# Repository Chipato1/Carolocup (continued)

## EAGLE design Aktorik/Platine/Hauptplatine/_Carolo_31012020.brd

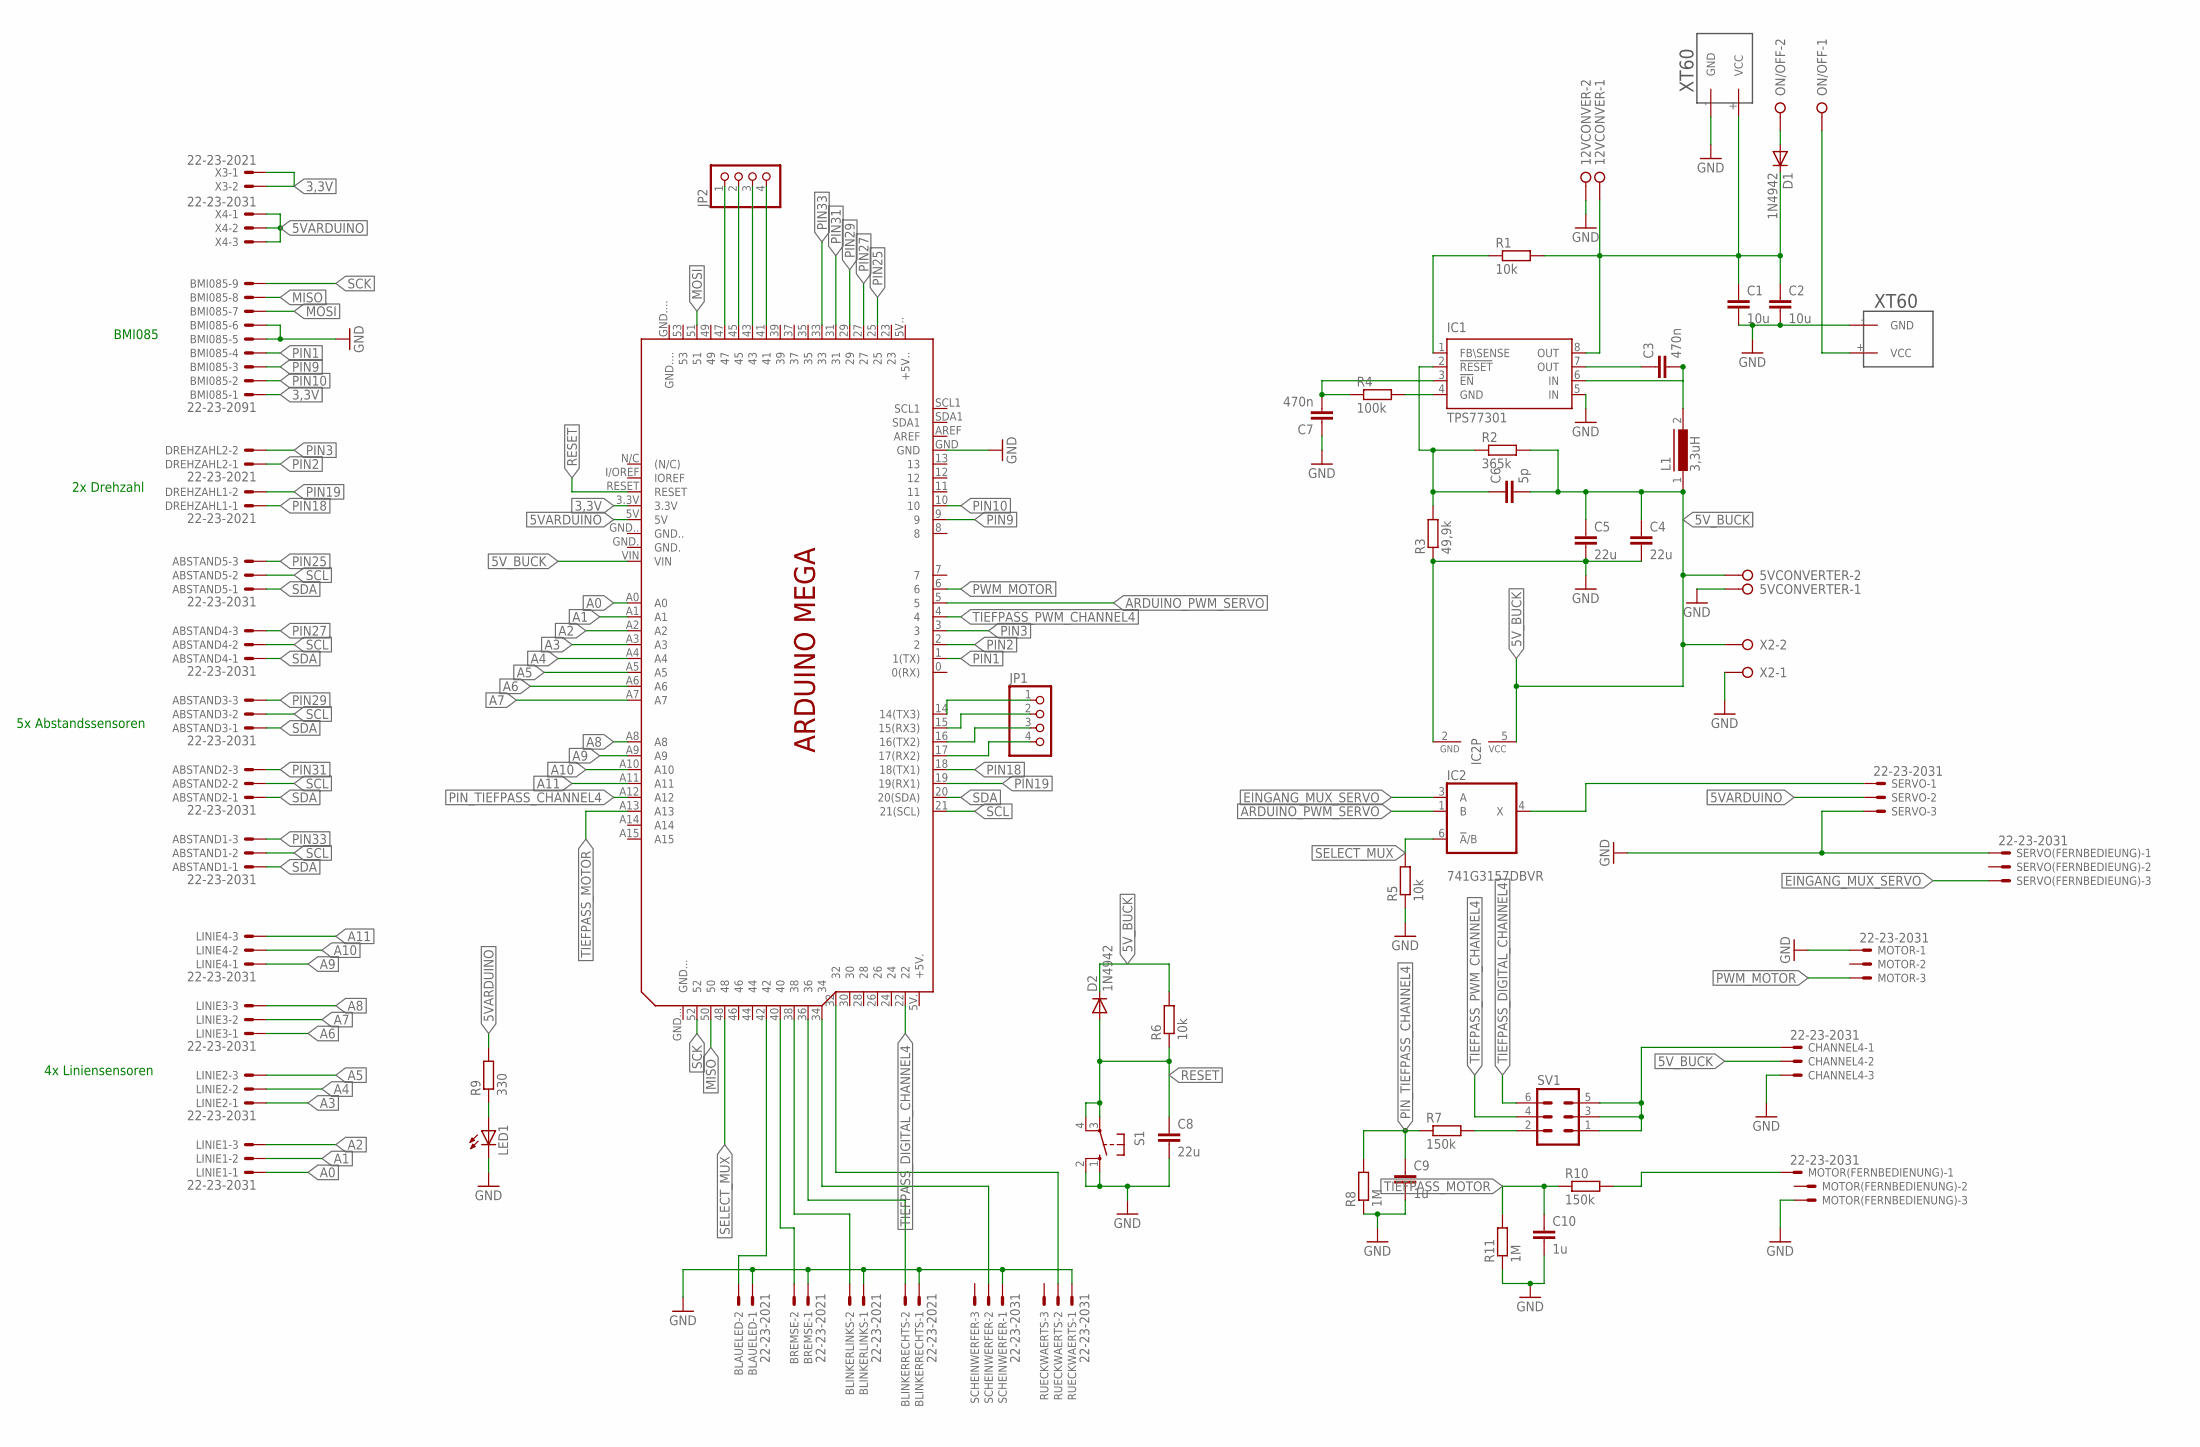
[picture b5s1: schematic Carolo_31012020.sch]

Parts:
5VCONVERTER, 12VCONVER: W237-02P; W237-132
ABSTAND1, ABSTAND2, ABSTAND3, ABSTAND4, ABSTAND5: 22-23-2031
BLAUELED: 22-23-2021
BLINKERLINKS: 22-23-2021
BLINKERRECHTS: 22-23-2021
BMI085: 22-23-2091
BREMSE: 22-23-2021
C1, C2: 10u; C2.5-3
C3, C7: 470n; C2.5-3
C4, C5, C8: 22u; C2.5-3
C6: 5p; C2.5-3
C9, C10: 1u; C2.5-3
CHANNEL4: 22-23-2031
D1, D2: 1N4942; DO41-10
DREHZAHL1, DREHZAHL2: 22-23-2021
IC1: TPS77301; SOP-08
IC2: 741G3157DBVR; DBV_R-PDSO-G6
JP1, JP2: PINHD-1X4; 1X04
L1: 3,3uH; 82114R
LED1: LED5MM
LINIE1, LINIE2, LINIE3, LINIE4: 22-23-2031
MOTOR: 22-23-2031
MOTOR(FERNBEDIENUNG): 22-23-2031
ON/OFF: W237-02P; W237-132
PCB1: ARDUINO_MEGA
R1, R5, R6: 10k; 0411/15
R2: 365k; 0411/15
R3: 49,9k; 0411/15
R4: 100k; 0411/15
R7, R10: 150k; 0411/15
R8, R11: 1M; 0411/15
R9: 330; 0411/15
RUECKWAERTS: 22-23-2031
S1: 10-XX; B3F-10XX
SCHEINWERFER: 22-23-2031
SERVO: 22-23-2031
SERVO(FERNBEDIEUNG): 22-23-2031
SV1: ML6
U$1, U$2: XT60
X2: W237-02P; W237-132
X3: 22-23-2021
X4: 22-23-2031

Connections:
3,3V: BMI085.1, PCB1.3.3V, X3.1, X3.2
5VARDUINO: PCB1.5V, R9.2, SERVO.2, X4.1, X4.2, X4.3
5V_BUCK: 5VCONVERTER.2, C4.1, C5.1, C6.2, CHANNEL4.2, D2.C, IC2.5 (VCC), L1.1, PCB1.VIN, R2.2, R6.2, X2.2
A0: LINIE1.1, PCB1.A0
A1: LINIE1.2, PCB1.A1
A2: LINIE1.3, PCB1.A2
A3: LINIE2.1, PCB1.A3
A4: LINIE2.2, PCB1.A4
A5: LINIE2.3, PCB1.A5
A6: LINIE3.1, PCB1.A6
A7: LINIE3.2, PCB1.A7
A8: LINIE3.3, PCB1.A8
A9: LINIE4.1, PCB1.A9
A10: LINIE4.2, PCB1.A10
A11: LINIE4.3, PCB1.A11
ARDUINO_PWM_SERVO: IC2.1 (B), PCB1.5
EINGANG_MUX_SERVO: IC2.3 (A), SERVO(FERNBEDIEUNG).3
GND: 5VCONVERTER.1, 12VCONVER.2, BLAUELED.1, BLINKERLINKS.1, BLINKERRECHTS.1, BMI085.5, BMI085.6, BREMSE.1, C1.2, C2.2, C4.2, C5.2, C7.1, C8.2, C9.2, C10.2, CHANNEL4.3, IC1.5 (IN), IC2.2 (GND), LED1.K (C), MOTOR.1, MOTOR(FERNBEDIENUNG).3, PCB1.GND, R3.1, R5.1, R8.1, R11.1, RUECKWAERTS.1, S1.1 (S), S1.2 (S1), SCHEINWERFER.1, SERVO.3, SERVO(FERNBEDIEUNG).1, U$1.- (GND), U$2.- (GND), X2.1
MISO: BMI085.8, PCB1.50; also elsewhere on the board
MOSI: BMI085.7, PCB1.51
unnamed: ON/OFF.1, U$1.+ (VCC)
unnamed: IC2.4 (X), SERVO.1
unnamed: R7.2, SV1.2
unnamed: C6.1, IC1.2 (!RESET), R2.1, R3.2
unnamed: C3.1, IC1.7 (OUT)
unnamed: CHANNEL4.1, SV1.1, SV1.3, SV1.5
unnamed: PCB1.32, RUECKWAERTS.2
unnamed: C3.2, IC1.6 (IN), L1.2
unnamed: C7.2, IC1.3 (!EN), R4.1
unnamed: PCB1.34, SCHEINWERFER.2
unnamed: BLINKERRECHTS.2, PCB1.36
unnamed: BLINKERLINKS.2, PCB1.38
unnamed: LED1.A, R9.1
unnamed: BLAUELED.2, PCB1.42
unnamed: BREMSE.2, PCB1.40
unnamed: JP2.4, PCB1.41
unnamed: IC1.4 (GND), R4.2
unnamed: D1.A, ON/OFF.2
unnamed: JP2.3, PCB1.43
unnamed: 12VCONVER.1, C1.1, C2.1, D1.C, IC1.8 (OUT), R1.2, U$2.+ (VCC)
unnamed: MOTOR(FERNBEDIENUNG).1, R10.2
unnamed 48: JP2.2, PCB1.45; also elsewhere on the board
unnamed 49: JP2.1, PCB1.47; also elsewhere on the board
unnamed: IC1.1 (FB\SENSE), R1.1
unnamed: JP1.1, PCB1.14 (14(TX3))
unnamed: JP1.2, PCB1.15 (15(RX3))
unnamed: JP1.3, PCB1.16 (16(TX2))
unnamed: JP1.4, PCB1.17 (17(RX2))
PIN1: BMI085.4, PCB1.1 (1(TX))
PIN2: DREHZAHL2.1, PCB1.2
PIN3: DREHZAHL2.2, PCB1.3
PIN9: BMI085.3, PCB1.9
PIN10: BMI085.2, PCB1.10
PIN18: DREHZAHL1.1, PCB1.18 (18(TX1)); also elsewhere on the board
PIN19: DREHZAHL1.2, PCB1.19 (19(RX1)); also elsewhere on the board
PIN25: ABSTAND5.3, PCB1.25
PIN27: ABSTAND4.3, PCB1.27
PIN29: ABSTAND3.3, PCB1.29
PIN31: ABSTAND2.3, PCB1.31
PIN33: ABSTAND1.3, PCB1.33
PIN_TIEFPASS_CHANNEL4: C9.1, PCB1.A12, R7.1, R8.2
PWM_MOTOR: MOTOR.3, PCB1.6
RESET: C8.1, D2.A, PCB1.RESET, R6.1, S1.3, S1.4 (P1)
SCK: BMI085.9, PCB1.52
SCL: ABSTAND1.2, ABSTAND2.2, ABSTAND3.2, ABSTAND4.2, ABSTAND5.2, PCB1.21 (21(SCL))
SDA: ABSTAND1.1, ABSTAND2.1, ABSTAND3.1, ABSTAND4.1, ABSTAND5.1, PCB1.20 (20(SDA))
SELECT_MUX: IC2.6 (!A!/B), PCB1.48, R5.2
TIEFPASS_DIGITAL_CHANNEL4: PCB1.22, SV1.6
TIEFPASS_MOTOR: C10.1, PCB1.A13, R10.1, R11.2
TIEFPASS_PWM_CHANNEL4: PCB1.4, SV1.4

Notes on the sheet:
BMI085
2x Drehzahl
5x Abstandssensoren
4x Liniensensoren

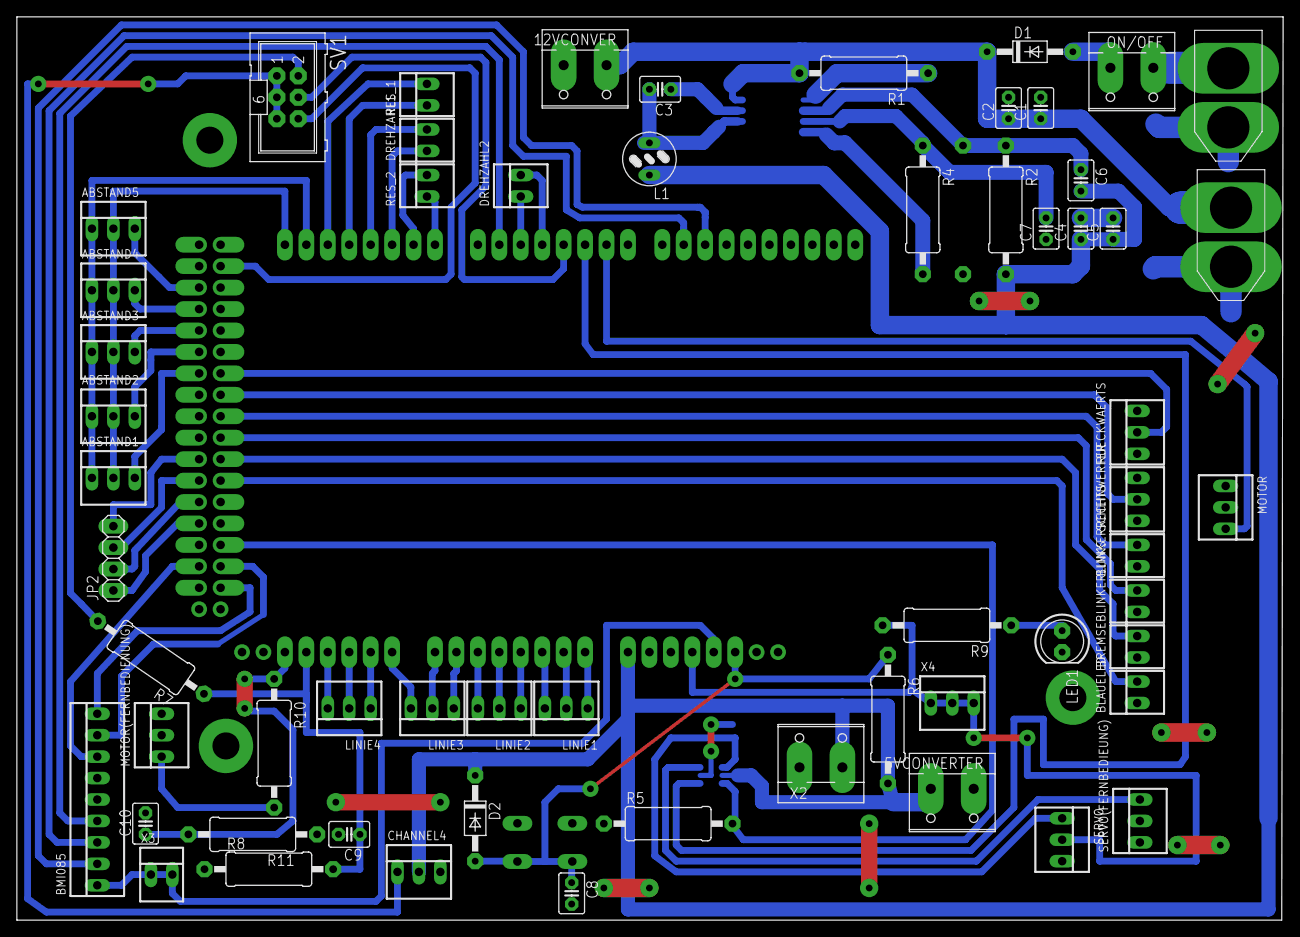
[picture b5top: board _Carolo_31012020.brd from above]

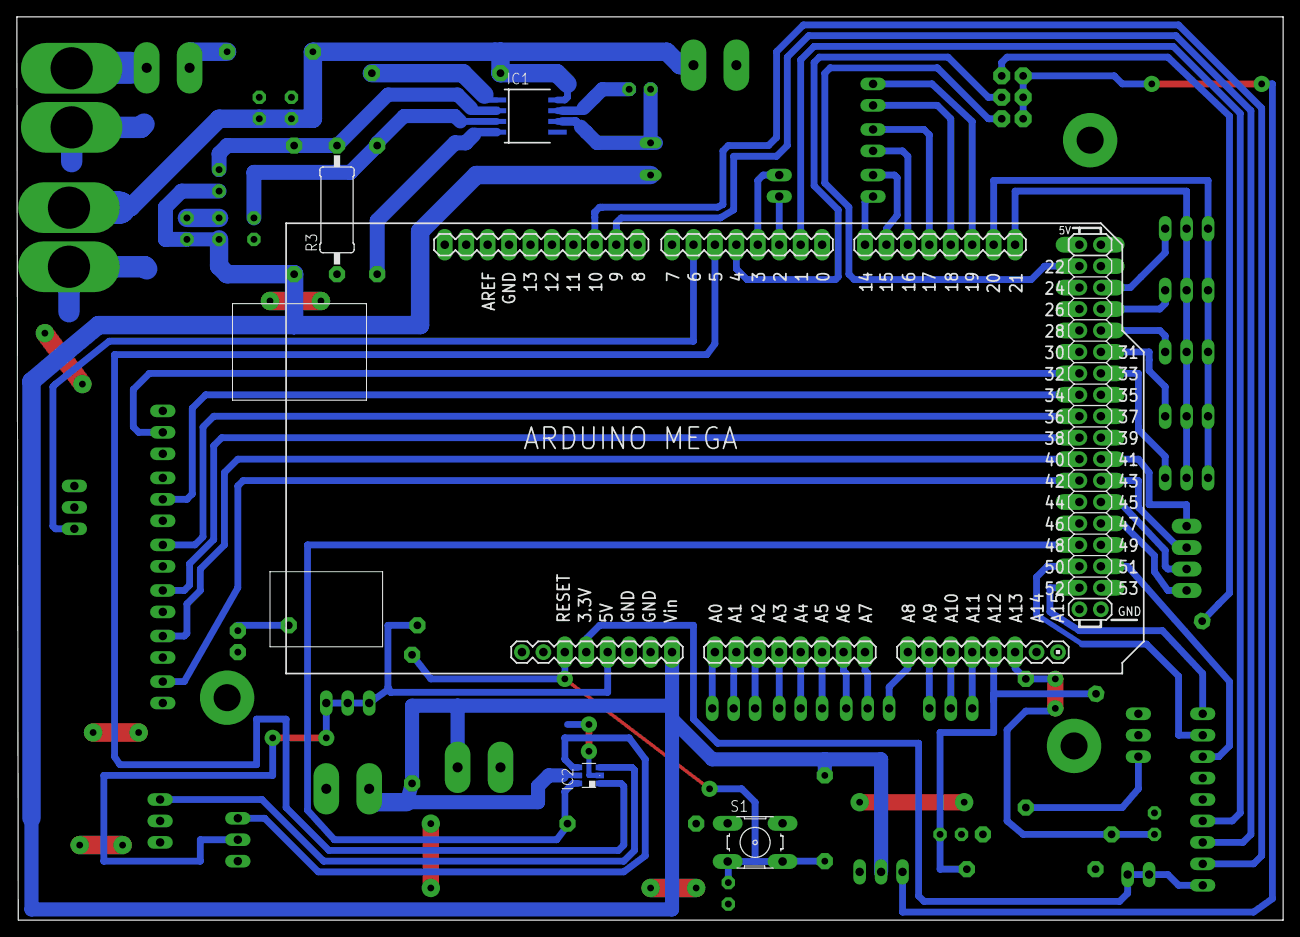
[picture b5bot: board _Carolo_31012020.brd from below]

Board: 2 copper layers, 150.0 x 107.0 mm, 64 parts (5 on the bottom side), 34 nets.

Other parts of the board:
E$1: ARDUINO_MEGA
RES_1, RES_2: 22-23-2021

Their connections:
MISO: E$1.50; also elsewhere on the board
unnamed 48: E$1.45; also elsewhere on the board
unnamed 49: E$1.47; also elsewhere on the board
PIN18: E$1.16; also elsewhere on the board
PIN19: E$1.17; also elsewhere on the board
S$1: E$1.19, RES_1.2
S$2: E$1.18, RES_1.1
S$3: E$1.15, RES_2.2
S$4: E$1.14, RES_2.1

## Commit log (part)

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2020-01-18 Added Start box detection
2020-01-18 Added new nodes
2020-01-18 Update CMakeLists
2020-01-18 Rename
2020-01-18 Name fix
2020-01-18 Name
2020-01-18 Typo
2020-01-18 Aktuell benötigte Nodes für die Kameraerkennung
2020-01-18 Create test
2020-01-18 new Upload
2020-01-18 Zweite Platine fertig
2020-01-20 ros erstellt
2020-01-20 Updated lane detection
2020-01-20 Added image proc
2020-01-20 Added launch script
2020-01-20 Kamera eingestellt und config hinzugefügt
2020-01-20 Config fix
2020-01-20 Fix for new clothoid model
2020-01-20 Added image view
2020-01-20 Added calibrate script
2020-01-20 Mem opti
2020-01-20 GPU Optimierungen
2020-01-20 Bug fix
2020-01-20 files
2020-01-20 RC motor hinzugefügt
2020-01-20 lichter knoten verschoben
2020-01-20 Revert "files"
    This reverts commit 8bc4316fc82aa183934083b4fa9890b025077f60.
2020-01-20 Revert "Merge pull request #60 from Chipato1/spurerkennung"
    This reverts commit 08e747200bb99e5533f0eb1627566205d3175c71, reversing
    changes made to ee4637fffe4195ab343a74071d12329f193db9f8.
2020-01-20 patch
2020-01-20 Gitignore CMakeLists.txt
2020-01-20 Added the stuff Alex deleted
2020-01-20 Commit für Branch
2020-01-20 test version
2020-01-20 Revert "patch"
    This reverts commit a01900fcba367d84bb3aac4d98ac42adad781406.
2020-01-20 Push it!
2020-01-20 alles murks
2020-01-21 Kamera neu eingestellt
2020-01-21 Fail
2020-01-21 rosserial als Paket abgelegt
2020-01-21 rosserial als Paket abgelegt und jetzt auch geaddet
2020-01-21 added behavior tree to master
2020-01-22 patch2.0
2020-01-22 revision abgeschlossen, erfolgreiches überprüfen
2020-01-22 Versuch
2020-01-22 Patch für Arduino und Tester Node
2020-01-22 ros anpassungen
2020-01-22 Created trajectory node; removed empty Behavior-Tree node
2020-01-23 kommentare hinzugefügt+RC mode fix
2020-01-23 Update algorithm & added ros package
2020-01-23 Updated launch script
2020-01-23 Added compiler flags
2020-01-23 Add files via upload
    arduino code sensorik
2020-01-23 Add files via upload
    Code for whole arduino (sensorik and aktorik)
2020-01-23 names changed
2020-01-23 name changed
2020-01-23 imu and tof fixed
2020-01-23 Updated ROS node
2020-01-23 Updated package
2020-01-23 CMAKE
2020-01-23 test
2020-01-23 add a pkg for controlling the arduino lights
2020-01-23 Bug fixes
2020-01-24 finale Platinenpläne
2020-01-24 fix Platineordner
2020-01-24 correct Arduino alder + Testknoten für altes Interface
2020-01-24 correct Arduino
2020-01-25 Changes?
2020-01-25 Added packages to ros core
2020-01-25 Update gitignore
2020-01-26 Updated camera launch file
2020-01-26 Test of service
2020-01-26 Zustandsraum überarbeitet
2020-01-26 Crazy shit
2020-01-26 Removed unneccesary package
2020-01-26 Copied to Catkin workspace
2020-01-26 Removed unused files
2020-01-26 chmod
2020-01-26 chmod 2
2020-01-26 statemachine ueberbleibsel
2020-01-26 optimiert und getestet
2020-01-26 PI regler and sm
2020-01-26 Zustandsraummodell erster ROS Entwurf
2020-01-27 bild erstellt
2020-01-27 pt1 glied des motors neu angenähert
2020-01-27 anpassung rc mode
2020-01-27 Kamera eingestellt
2020-01-27 added decision making
2020-01-27 filter überprüft
2020-01-28 irgend nen autosave...
2020-01-28 added topic for each signal
2020-01-28 deleted old file
2020-01-28 arduino pins updated
2020-01-28 topic names updated
2020-01-28 added state-machine node
2020-01-28 more sm
2020-01-28 fuer alex die bitch
2020-01-28 State Machine aufgesetzt; Spezifikation für Init, Fahren und Kreuzungen. Noch ohne State Estimation.
2020-01-29 Added message
2020-01-29 Added logging
2020-01-29 rcmodepublisher + anpassung schwellenspannung tiefpass
2020-01-29 Anpassung der ROS Topics
2020-01-29 ROS aktualisiert
2020-01-29 Filter für Raddrehzahl hinzugefügt
2020-01-29 Stanley auf rad angepasst, Filter getestet
2020-01-30 rc mode channel 4 hinzugefügt
2020-01-30 datentypen atualisiert
2020-01-30 Fixes
2020-01-30 Added pinhole camera
2020-01-30 topic namen angepasst, verbessert und neu erstellt
2020-01-30 imu and qtr removed
2020-01-31 added ros::rate
2020-01-31 Added Hough
2020-01-31 viel pfusch
2020-01-31 Started implementing state estimation and trajectory templates. UNTESTED.
2020-02-01 New test
2020-02-01 FIX damn double math error!
2020-02-01 added correct Signal names and ROS problems ...Code will not work if the TOFs does not work .. not testet
2020-02-01 forgot intialzation
2020-02-02 topic names changed, aktorik and sensorik in one node
2020-02-02 Ausreißererkennung in x hinzugefügt
2020-02-02 Dump Codereste
2020-02-02 Update print
2020-02-02 Revert "merge commit"
    This reverts commit e9751b27b35cbfba70e64008ffd2a4dda1d567dd.
2020-02-02 Manual merge
2020-02-02 Added CMakeLists.txt
2020-02-02 Removed bugs
2020-02-02 Updated config.cfg
2020-02-02 added corrections to arduino code
2020-02-02 Removed msg from file
2020-02-02 Removed old Spurerkennung folder
2020-02-02 Added launchInfo.txt
2020-02-02 neue motorkennlinie
2020-02-02 neue rosnodes mit angepassten namen
2020-02-03 Unnoetige Build und Devel Ordner gelöscht
2020-02-03 Removed left lane
2020-02-03 Added dx limitation
2020-02-03 Suchfelder x+y hinzugefügt
2020-02-03 Fix suchfenster
2020-02-03 Fehler im Algorithmus behoben
2020-02-03 Koordinatentransformation geändert
2020-02-03 plot der motorkennlinie verändert
2020-02-03 aktorik
2020-02-03 Restore versuch 1
2020-02-03 ANpassung an OpenCV 4
2020-02-03 Fixed
2020-02-03 Removed unused packages
2020-02-03 Revert "Merge branch 'master' into state_machine_ext"
    This reverts commit 646ef8fc10ac33197949a1d7599e6aa46672742d, reversing
    changes made to c686b8f9acd174707dd55589d6bbfb231dd0d6af.
2020-02-03 Revert "Revert "Merge branch 'master' into state_machine_ext""
    This reverts commit 53e2e90ab2c88c406457ec8ca4d52494c76b056a.
2020-02-03 Revert "Revert "Revert "Merge branch 'master' into state_machine_ext"""
    This reverts commit 84697a0dc7f9e0ef6174af521e42b328eee03918.
2020-02-03 rc mode updated
2020-02-03 Fix master branch
2020-02-03 Added install folder to gitignore
2020-02-03 Quick Fix
2020-02-03 Aktorik und Abstandssensorik auf lauffähigem Stand, todo: RPM
2020-02-03 ROS Modell Längssteuerung gebildet
2020-02-03 Aktorik values updated
2020-02-04 rpm software adapted to new sensor
2020-02-04 First implementation mit mutex
2020-02-04 ROS Modell Steuerung eingefügt in Filter
2020-02-04 Multithreading izz da
2020-02-04 Upload ROS files 1
2020-02-04 Upload ROS files 2
2020-02-04 Fixed build errors
2020-02-04 Bugfixes
2020-02-04 brake richtig schreiben
2020-02-04 Added Lights
2020-02-04 Regler Nodes
2020-02-05 rpm software adapted
2020-02-05 Längssteuerung und Solver-Zeiten angepasst
2020-02-05 Stanley Sollgeschweindigkeit
2020-02-05 aktueller Stand
2020-02-05 Querregler und LängsSTEUERUNG in catkin_ws hinzugefügt
2020-02-05 anleitung für regler init
2020-02-05 minimale anpassungen
2020-02-05 Regler mit angepasster raddrehzahlmessung und filterung. Tatsächliche REGLUNG, keine Steuerung
2020-02-05 ROS README
2020-02-05 modelle neu gebaut mit 100hz OHNE anti wind up
2020-02-05 finaer stand 1
2020-02-05 Added Buttons
2020-02-06 regler auf neue einheiten angepasst und frequenz verändert
2020-02-06 roscode
2020-02-06 Servonullstellung einstellen
2020-02-06 Nullstellung Optimierung 2
2020-02-06 vergessen zu speichern
2020-02-06 Reverse Light Implementation
2020-02-06 lauffähiger Stand
2020-02-06 Revert "lauffähiger Stand"
    This reverts commit 34f1ebdca5c0aa4428d648066d3a987aa67797dd.
2020-02-06 zusammengefuegt
2020-02-06 Fixed PointLaneDetector
2020-02-06 Vision integration
2020-02-06 Config update
2020-02-06 Add to config file
2020-02-06 added RC Impovments
2020-02-06 mux h l tausch
2020-02-06 adapted rpm software
2020-02-06 add drive mode
2020-02-06 Implemented Clothoide
2020-02-06 new Pins
2020-02-06 patch motor
2020-02-07 filterung
2020-02-07 schwächere Filterung
2020-02-07 regler darauf
2020-02-07 arduino code in Master 'gemergt'
2020-02-07 diverse Aenderungen
2020-02-07 master last jetson
2020-02-07 Funktionsfähige Steuerung, falls Regelung abschmiert
    Funktionsfähige Steuerung mit Längsregler und Querregler
2020-02-07 Steuerung dem Branch hinzugefügt
2020-02-07 Added ros message to stoplinhe detector
2020-02-07 regler auf 50hz angepasst - immer noch zu schnell?
2020-02-07 Regler 50Hz Ros-code
2020-02-07 Parameter update
2020-02-07 arduino tests
2020-02-07 fix bugs
2020-02-07 regler 20 hz
2020-02-07 regler 20hz ros code
2020-02-07 Optimise Stopdetection and qr Code
2020-02-07 Updated the new thresholding algorithms
2020-02-07 Edit sm to launch info
2020-02-08 Pure-Pursuit-Regler-Modell entworfen
2020-02-08 Fix 1
2020-02-08 Several fixes
2020-02-08 Git fix 892947938274928374
2020-02-08 regler auf 50hz und höheren i anteil und reset des i anteils bei rc mode
2020-02-08 finaler regler von robert in /catkin_0802_final_robert mit 50hz frequenz, höherem I anteil und reset des I anteils bei rc mode
2020-02-08 new zbar qrCode
2020-02-08 Fixed regelung amk ihr Nudelköpfe --Albert Einstein
2020-02-08 fixed qr a little
2020-02-08 fix bugs2
2020-02-08 tested stopline
2020-02-08 Fixes in Arduino code
2020-02-08 regler parameter rückgängig gemacht
2020-02-08 regler parameter rückgängig gemacht, 20hz mit reset von i anteil . catkin hinzugefügt
2020-02-09 Minor update
2020-02-09 Upload
2020-02-09 Rückfahrlicht
2020-02-09 Update lichter
2020-02-09 added alex mum
2020-02-09 Path update
2020-02-09 Fuer Carl aus ehrenbasis
2020-02-09 add maxis mum to porn
2020-02-09 neue software für tof sensoren
2020-02-09 Update launch_car
2020-02-09 added max treshold +-137 for servo in aktorik code and watchdog in ROS_Code -> bewaregit pull Watchdog is not stable
2020-02-10 mued
2020-02-10 watch away
2020-02-10 QR Working
2020-02-10 Update 2
2020-02-10 removed camera
2020-02-10 Buggy
2020-02-10 Mutex added
2020-02-10 Pfusch
2020-02-10 servo formel neu
2020-02-10 angepasst
2020-02-10 tof publisher
2020-02-10 laufzeitmessung
2020-02-10 sm fixes
2020-02-10 Längsregler angepasst, nicht signifikante änderungen
2020-02-10 optimierung
2020-02-10 tof updated
2020-02-10 watchdog-bitch
2020-02-10 Fixed TOFs in state machine
2020-02-10 bennis MUM
2020-02-10 Implemented QR Code
2020-02-10 First try
2020-02-10 Update 1
2020-02-10 Update 3
2020-02-10 keine wirklichen änderungen
2020-02-10 stanley stabil
2020-02-10 Fixed Regelung and added launch file
2020-02-10 Stanley jetzt mit neuem x vor Fahrzeughinterachse: 50cm!!!
2020-02-10 Good SM
2020-02-11 Crossing
2020-02-11 Guter stand amk
2020-02-11 rpm removed
2020-02-11 lights fixed
2020-02-11 stopline added
2020-02-14 autosave regler
2020-02-14 ROS auf WSL getestet
2020-02-20 pid regler mittels pid-tuner von matlab optimiert
2020-02-20 aufgeräumt
2020-02-24 1 file all models
2020-03-04 kleinigkeiten angepasst und ausprobiert
2020-03-05 MPC regler und tuner mit matlab getestet, ergebniss ausbaufähig
2020-03-05 nochmal getestet - wird noch einige von diesen commits geben
2020-03-07 an der motorkennlinie rumgespielt
2020-04-18 Massive Refactoring
2020-04-23 changed model language to english
2020-04-23 added plant model of BLDC to Regler/Laengs..
2020-04-26 neue kennlinie erstellt
2020-04-26 Fuzzy System erstellt
2020-04-26 just played a little bit
2020-04-30 changed fis
2020-05-01 Added awsome fuzzy adaption to PI controller
2020-05-01 Fuzzy changed, fuzzy finished
2020-05-01 minor changes
2020-05-04 added parking and modified model_all file
2020-05-04 Modified model_all-file
2020-05-06 new time discrete MPC and time independent state space
2020-05-06 showed mpc to benne - he completly lost his mind!
2020-05-08 model_all-file structorized
2020-05-09 optimized model_all-file structure
2020-05-09 lidar ros package added
2020-05-09 readme file updated
2020-05-09 folder structure changed
2020-05-09 readme file modified
2020-05-10 optimized mpc
2020-05-10 saved matlab.mat
2020-05-10 changed lateral control from Stanley to MPC
2020-05-11 nothing important
2020-05-11 added psif as state to mpc
2020-05-11 explicit mpc controller tested
2020-05-11 eMPC tested for thesis
2020-07-02 Push auf Repo, Vision V2
